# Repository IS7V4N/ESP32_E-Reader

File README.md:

# ESP32 E-Reader

A custom-built e-ink reading device based on the ESP32-C3, designed for everyday use. Built around a 4.2" e-ink display with a frontlight for reading in the dark environment, running a modified version of the [Crosspoint](https://github.com/crosspoint-reader/crosspoint-reader) open-source firmware adapted for custom hardware. The goal was to build a capable, low-cost alternative to commercial e-readers with full control over both hardware and software.

---
## Hardware License

The hardware designs in `/Hardware` are licensed under the
[CERN-OHL-W v2](Hardware/LICENSE).

## Hardware

> Building your own? See the [Build guide](Hardware/docs/Build%20guide.md) for step-by-step assembly instructions.

| Component  | Details                                             |
| ---------- | --------------------------------------------------- |
| MCU        | ESP32-C3 (4MB flash)                                |
| Display    | Good Display 4.2" grayscale e-ink panel             |
| Storage    | SD card (books, cache, user settings)               |
| Frontlight | TI TPS61169 PWM-controlled LED driver, 15V boost    |
| Battery    | 700mAh LiPo                                         |
| USB        | USB-C (charging + native USB via differential pair) |
| PCB        | 4-layer, custom KiCad design (Rev. B)               |

### PCB stack-up

```
F.Cu     — signal
GND      — full ground plane
PWR      — power distribution
B.Cu     — signal
```

Ground pour with stitching vias on both outer layers. EMI-sensitive boost converter traces kept compact.

### Power rails

| Rail     | Source                     | Purpose               |
| -------- | -------------------------- | --------------------- |
| 3.4–4.2V | LiPo battery               | System input          |
| 3.3V     | LDO                        | ESP32-C3, logic       |
| 5V       | USB-C input                | Charging              |
| ±20V     | Boost converter            | E-ink panel driver    |
| 15V      | Boost converter (TPS61169) | Frontlight LED driver |

### Power management

Three operating states optimized for battery life:

| State      | Description                                     | Wake latency |
| ---------- | ----------------------------------------------- | ------------ |
| Active     | Full speed, display updating                    | —            |
| Sleep      | Reduced CPU clock, peripherals idle             | Fast         |
| Deep sleep | µA range consumption, triggered by power button | Slow         |

The device enters Sleep automatically after a display update completes. Deep sleep is only used when powered off via the power button.

### Controls

| Button                        | Function                                                         |
| ----------------------------- | ---------------------------------------------------------------- |
| Left / Right / Back / Confirm | Context-sensitive navigation (current function shown on display) |
| Power button                  | Short press: page turn / Long press: power on/off                |

---

## Firmware

Based on [Crosspoint Reader](https://github.com/crosspoint-reader/crosspoint-reader) with modifications for custom hardware and 4MB flash constraint.

### What's changed from upstream

- **HalFrontlight** — new HAL driver for PWM-controlled frontlight via TPS61169
- **HalPowerManager** — smaller tweaks
- **HalGPIO** — GPIO, button layout adapted to custom PCB
- **partitions_4mb.csv** — custom partition scheme to fit 4MB flash (replaces upstream 16MB default)
- **platformio.ini** — 4MB build configuration
- **Display refresh** — modified refresh handling for Good Display 4.2" panel compatibility
- **Dictionary** — English → Hungarian word lookup in the EPUB reader (see [Dictionary](#dictionary))

See [`docs/4mb-build/`](Software/crosspoint-reader/docs/4mb-build/) for detailed documentation on the 4MB build process and known issues.

## Dictionary

Long-press **Confirm** (0.5 s) in an EPUB to enter dictionary mode. The four front buttons become a cursor:

| Button (left to right) | Short press  | Long press                  |
| ---------------------- | ------------ | --------------------------- |
| Left                   | cursor left  | —                           |
| Back                   | cursor up    | leave dictionary mode       |
| Confirm                | cursor down  | translate the selected word |
| Right                  | cursor right | —                           |

The translation (a few Hungarian words) appears in a popup, any button closes it.

The dictionary is a file on the SD card, `/dict/en-hu.dic` (about 4 MB, 118 000 word forms incl. inflections). It is
built on a PC with [`scripts/build_dict.py`](Software/crosspoint-reader/scripts/build_dict.py) from Wiktionary
(via [kaikki.org](https://kaikki.org)) with [FreeDict eng-hun](https://freedict.org) as a fallback; the script
documents the steps and the file format. Wiktionary data is CC BY-SA 4.0, FreeDict eng-hun is GPL-2.0+.

---

## Repository structure

```
ESP32_E-Reader/
├── Hardware/
│   ├── 3D CAD/                 — enclosure 3D models
│   ├── Bill Of Materials/      — BOM spreadsheets
│   ├── PCB/                    — KiCad project (Rev. B)
│   ├── REV-A/                  — Rev. A schematic/layout reference
│   └── LICENSE                 — CERN-OHL-W v2
├── Datasheets of Components/    — component datasheets (PDF)
└── Software/
    └── crosspoint-reader/       — firmware (fork of Crosspoint Reader)
        ├── src/                 — application source (activities, UI)
        ├── lib/                 — internal libraries (Epub engine, GfxRenderer, HAL, I18n)
        ├── open-x4-sdk/         — Xteink X4 community SDK (submodule)
        ├── docs/                — build docs, file formats, 4mb-build notes
        ├── scripts/             — build/codegen/debugging scripts
        ├── test/                — unit tests
        ├── platformio.ini       — build configuration
        └── LICENSE              — MIT
```

---

## Build

### Requirements

- [PlatformIO](https://platformio.org/)
- ESP32-C3 board with 4MB flash

### Steps

```bash
git clone https://github.com/IS7V4N/ESP32_E-Reader.git
cd ESP32_E-Reader
git submodule update --init --recursive
~/.platformio/penv/bin/pio run -e 4mb -t upload
```

---

## License
`/Hardware` are licensed under the
[CERN-OHL-W v2](Hardware/LICENSE).

Firmware modifications follow the license of the upstream [Crosspoint Reader](https://github.com/crosspoint-reader/crosspoint-reader) project.

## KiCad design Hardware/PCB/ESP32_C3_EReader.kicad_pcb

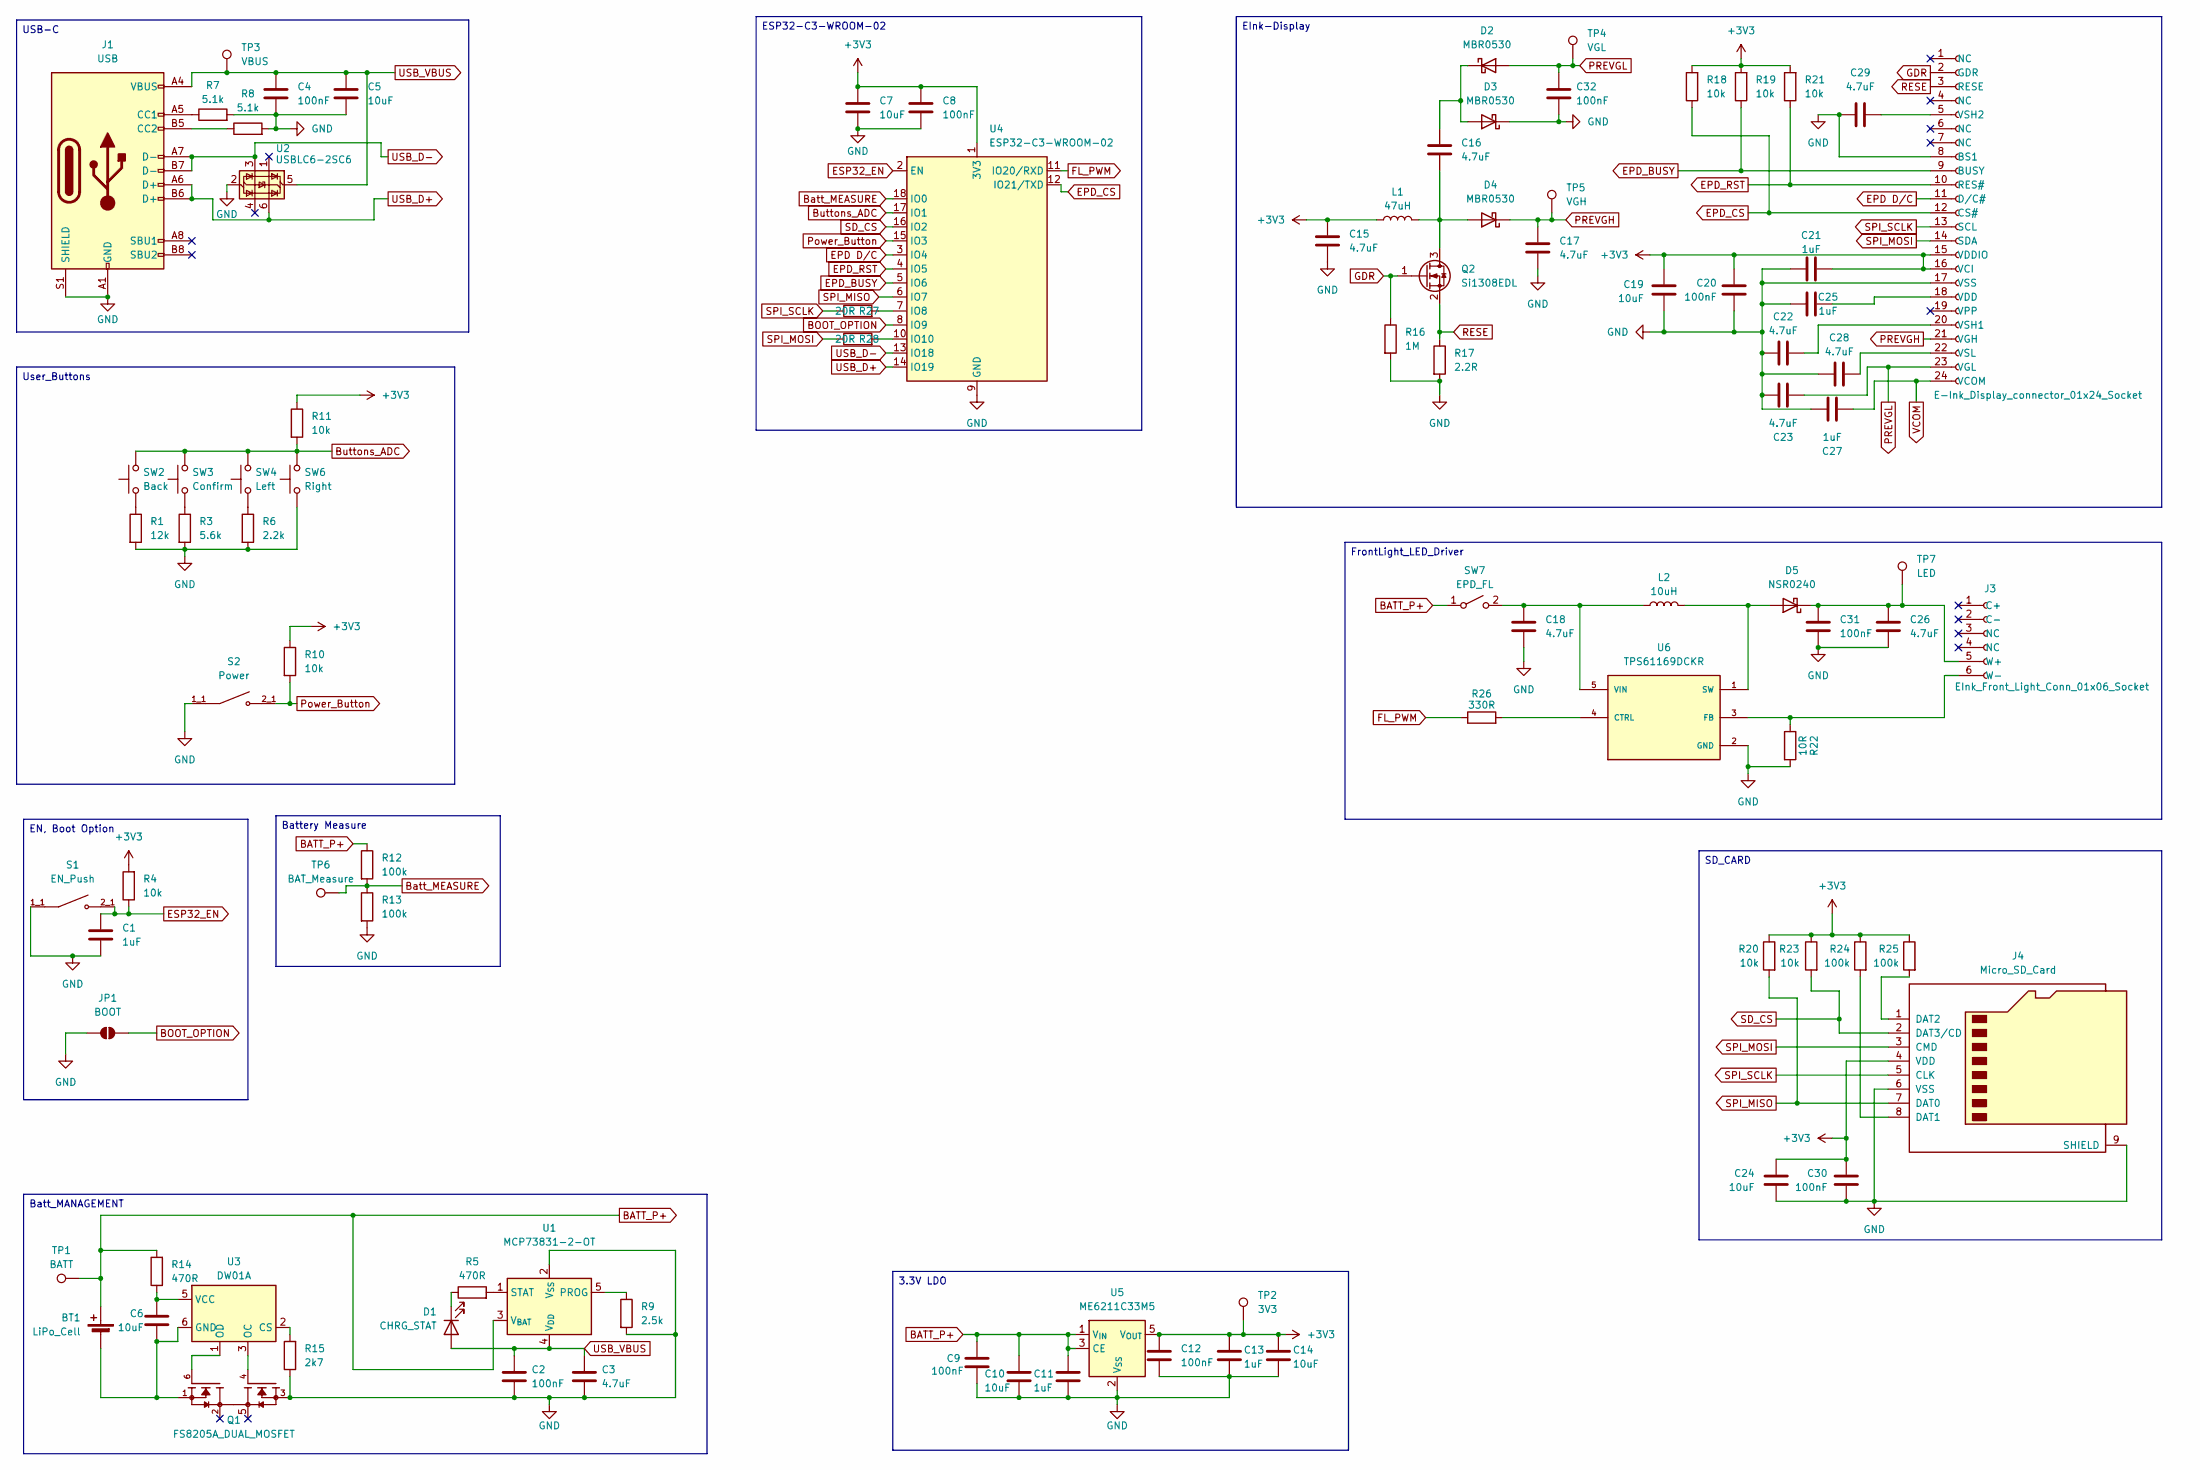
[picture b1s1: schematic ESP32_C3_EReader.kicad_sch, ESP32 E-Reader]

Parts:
BT1: LiPo_Cell; JST_PH_S2B-PH-K_1x02_P2.00mm_Horizontal
C1, C11, C13: 1uF; C_0603_1608Metric_Pad1.08x0.95mm_HandSolder
C2, C4, C8, C9, C12, C30: 100nF; C_0603_1608Metric_Pad1.08x0.95mm_HandSolder
C3, C15, C16, C17, C18, C22, C23, C26, C28, C29: 4.7uF; C_0805_2012Metric_Pad1.18x1.45mm_HandSolder
C5, C7, C10, C14, C24: 10uF; C_0603_1608Metric_Pad1.08x0.95mm_HandSolder
C6: 10uF; C_0603_1608Metric
C19: 10uF; C_0805_2012Metric_Pad1.18x1.45mm_HandSolder
C20: 100nF; R_0805_2012Metric_Pad1.20x1.40mm_HandSolder
C21, C25, C27: 1uF; C_0805_2012Metric_Pad1.18x1.45mm_HandSolder
C31, C32: 100nF; C_0805_2012Metric_Pad1.18x1.45mm_HandSolder
D1: CHRG_STAT; LED_0805_2012Metric_Pad1.15x1.40mm_HandSolder
D2, D3, D4: MBR0530; D_SOD-123
D5: NSR0240; D_SOD-323_HandSoldering
J1: USB; USB_C_Receptacle_GCT_USB4105-xx-A_16P_TopMnt_Horizontal
J2: E-Ink_Display_connector_01x24_Socket; Mirrored_Hirose_FH12-24S-0.5SH_1x24-1MP_P0.50mm_Horizontal
J3: EInk_Front_Light_Conn_01x06_Socket; XUNPU FPC-05FB-6PH20_1x06-1MP_P0.50mm_Horizontal
J4: Micro_SD_Card; microSD_HC_Hirose_DM3AT-SF-PEJM5
JP1: BOOT; SolderJumper-2_P1.3mm_Open_RoundedPad1.0x1.5mm
L1: 47uH; L_Panasonic_PCC-M0540M
L2: 10uH; L_Changjiang_FXL0420
Q1: FS8205A_DUAL_MOSFET; SOT-23-6_Handsoldering; PARTREV 1.7
Q2: Si1308EDL; SOT-323_SC-70
R1: 12k; R_0603_1608Metric_Pad0.98x0.95mm_HandSolder
R3: 5.6k; R_0603_1608Metric_Pad0.98x0.95mm_HandSolder
R4, R10, R11, R18, R19, R20, R21, R23: 10k; R_0603_1608Metric_Pad0.98x0.95mm_HandSolder
R5, R14: 470R; R_0603_1608Metric_Pad0.98x0.95mm_HandSolder
R6: 2.2k; R_0603_1608Metric_Pad0.98x0.95mm_HandSolder
R7, R8: 5.1k; R_0603_1608Metric_Pad0.98x0.95mm_HandSolder
R9: 2.5k; R_0603_1608Metric_Pad0.98x0.95mm_HandSolder
R12, R13, R24, R25: 100k; R_0603_1608Metric_Pad0.98x0.95mm_HandSolder
R15: 2k7; R_0603_1608Metric_Pad0.98x0.95mm_HandSolder
R16: 1M; R_0603_1608Metric_Pad0.98x0.95mm_HandSolder
R17: 2.2R; R_0805_2012Metric_Pad1.20x1.40mm_HandSolder
R22: 10R; R_0603_1608Metric_Pad0.98x0.95mm_HandSolder
R26: 330R; R_0603_1608Metric_Pad0.98x0.95mm_HandSolder
R27, R28: 20R; R_0603_1608Metric_Pad0.98x0.95mm_HandSolder
S1: EN_Push; SW_EVQ-P7C01P; PARTREV 2022.4
S2: Power; SW_EVQ-P7C01P; PARTREV 2022.4
SW2: Back; SW_SKRPACE010
SW3: Confirm; SW_SKRPACE010
SW4: Left; SW_SKRPACE010
SW6: Right; SW_SKRPACE010
SW7: EPD_FL; SW_SPDT_CK_JS102011SAQN
TP1: BATT; TestPoint_Pad_D1.5mm
TP2: 3V3; TestPoint_Pad_D1.5mm
TP3: VBUS; TestPoint_Pad_D1.5mm
TP4: VGL; TestPoint_Pad_D1.5mm
TP5: VGH; TestPoint_Pad_D1.5mm
TP6: BAT_Measure; TestPoint_Pad_D1.5mm
TP7: LED; TestPoint_Pad_D1.5mm
U1: MCP73831-2-OT; SOT-23-5
U2: USBLC6-2SC6; SOT-23-6
U3: DW01A; SOT-23-6
U4: ESP32-C3-WROOM-02
U5: ME6211C33M5; SOT-23-5
U6: TPS61169DCKR; SOT-353_SC-70-5; PARTREV A

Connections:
+3V3: C7.1, C8.1, C12.1, C13.1, C14.1, C15.1, C19.1, C20.1, C21.2, C24.1, C30.1, J2.15 (VDDIO), J2.16 (VCI), J4.4 (VDD), L1.1, R4.2, R10.1, R11.1, R18.2, R19.2, R20.1, R21.2, R23.1, R24.1, R25.1, TP2.1, U4.1 (3V3), U5.5 (V_{OUT})
BATT_P+: BT1.1 (+), C9.1, C10.1, C11.1, R12.1, R14.2, SW7.1 (A), TP1.1, U1.3 (V_{BAT}), U5.1 (V_{IN}), U5.3 (CE); also elsewhere on the board
BOOT_OPTION: JP1.2 (B), U4.8 (IO9)
Batt_MEASURE: R12.2, R13.1, TP6.1, U4.18 (IO0)
Buttons_ADC: R11.2, SW2.4, SW3.4 (2), SW4.4 (2), SW6.4 (2), U4.17 (IO1)
EPD D/C: J2.11 (D/C#), U4.3 (IO4)
EPD_BUSY: J2.9 (BUSY), R19.1, U4.5 (IO6)
EPD_CS: J2.12 (CS#), R18.1, U4.12 (IO21/TXD)
EPD_RST: J2.10 (RES#), R21.1, U4.4 (IO5)
ESP32_EN: C1.1, R4.1, S1.2_1, S1.2_2, U4.2 (EN)
FL_PWM: R26.1, U4.11 (IO20/RXD)
GDR: J2.2 (GDR), Q2.1 (G), R16.1
unnamed: D1.1 (K), R5.1
unnamed: C16.1, D2.1 (K), D3.2 (A)
unnamed: C16.2, D4.2 (A), L1.2, Q2.3 (D)
unnamed: D5.2 (A), L2.2, U6.1 (SW)
unnamed: C26.1, C31.1, D5.1 (K), J3.5 (W+), TP7.1
unnamed: J1.A5 (CC1), R7.1
unnamed: J1.B5 (CC2), R8.1
unnamed: C25.2, J2.18 (VDD)
unnamed: C22.2, J2.20 (VSH1)
unnamed: C29.2, J2.5 (VSH2)
unnamed: C28.2, J2.22 (VSL)
unnamed: J3.6 (W-), R22.1, U6.3 (FB)
unnamed: J4.8 (DAT1), R24.2
unnamed: J4.1 (DAT2), R25.2
unnamed: Q1.6 (G1), U3.1 (OD)
unnamed: Q1.4 (G2), U3.3 (OC)
unnamed: R1.1, SW2.1
unnamed: R3.1, SW3.1
unnamed: R6.1, SW4.1
unnamed 31: C18.1, L2.1, SW7.2 (B), U6.5 (VIN); also elsewhere on the board
unnamed: R9.1, U1.5 (PROG)
unnamed: R5.2, U1.1 (STAT)
unnamed: R15.2, U3.2 (CS)
unnamed: C6.1, R14.1, U3.5 (VCC)
unnamed: R27.2, U4.7 (IO8)
unnamed: R28.2, U4.10 (IO10)
unnamed: R26.2, U6.4 (CTRL)
PREVGH: C17.1, D4.1 (K), J2.21 (VGH), TP5.1
PREVGL: C23.2, C32.1, D2.2 (A), J2.23 (VGL), TP4.1
Power_Button: R10.2, S2.2_1, S2.2_2, U4.15 (IO3)
RESE: J2.3 (RESE), Q2.2 (S), R17.1
SD_CS: J4.2 (DAT3/CD), R23.2, U4.16 (IO2)
SPI_MISO: J4.7 (DAT0), R20.2, U4.6 (IO7)
SPI_MOSI: J2.14 (SDA), J4.3 (CMD), R28.1
SPI_SCLK: J2.13 (SCL), J4.5 (CLK), R27.1
USB_D+: J1.A6 (D+), J1.B6 (D+), U2.6 (I/O1), U4.14 (IO19)
USB_D-: J1.A7 (D-), J1.B7 (D-), U2.3 (I/O2), U4.13 (IO18)
USB_VBUS: C2.1, C3.1, C4.1, C5.1, D1.2 (A), J1.A4 (VBUS), J1.A9 (VBUS), J1.B4 (VBUS), J1.B9 (VBUS), TP3.1, U1.4 (V_{DD}), U2.5 (VBUS)
VCOM: C27.2, J2.24 (VCOM)

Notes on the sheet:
EN, Boot Option
3.3V LDO
EInk-Display
USB-C
SD_CARD
Batt_MANAGEMENT
User_Buttons
FrontLight_LED_Driver
Battery Measure
ESP32-C3-WROOM-02

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
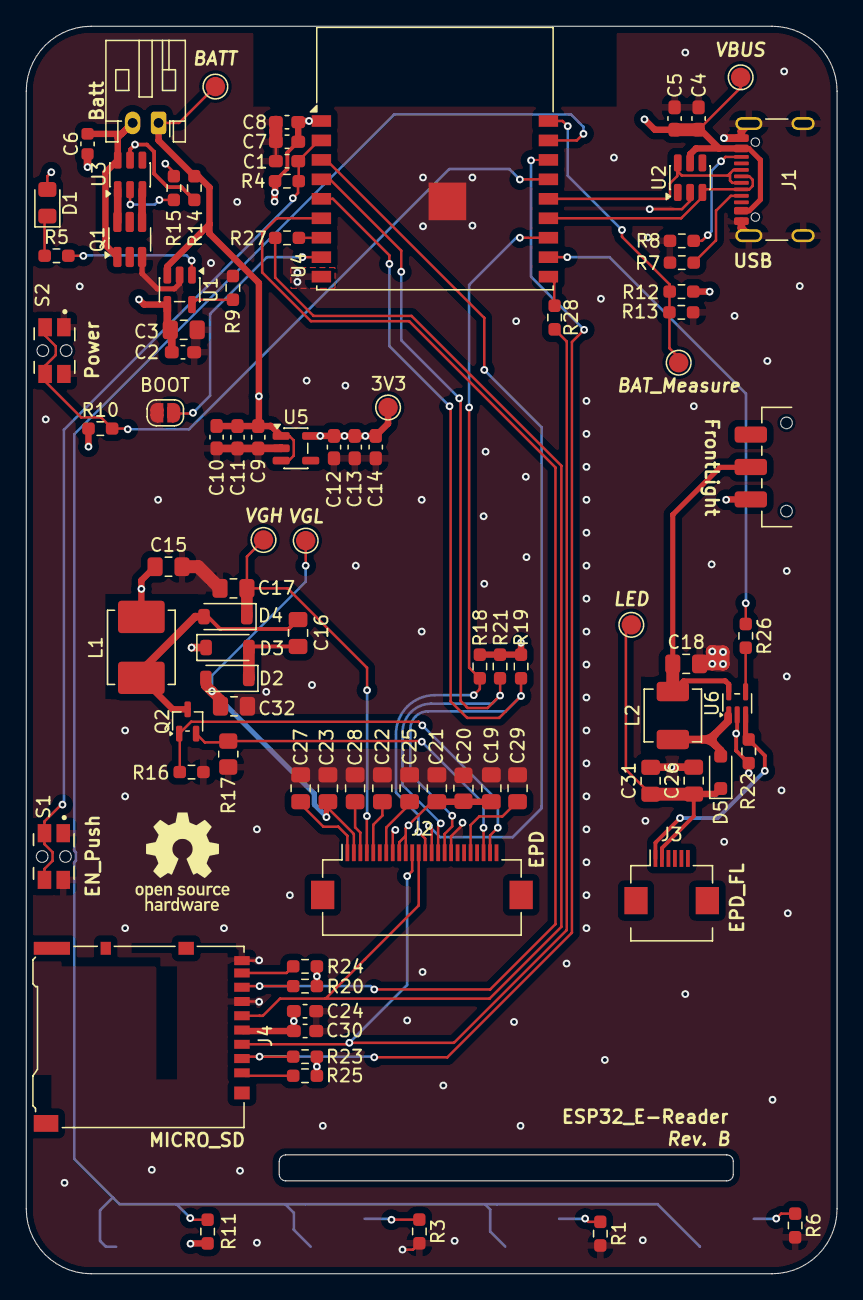
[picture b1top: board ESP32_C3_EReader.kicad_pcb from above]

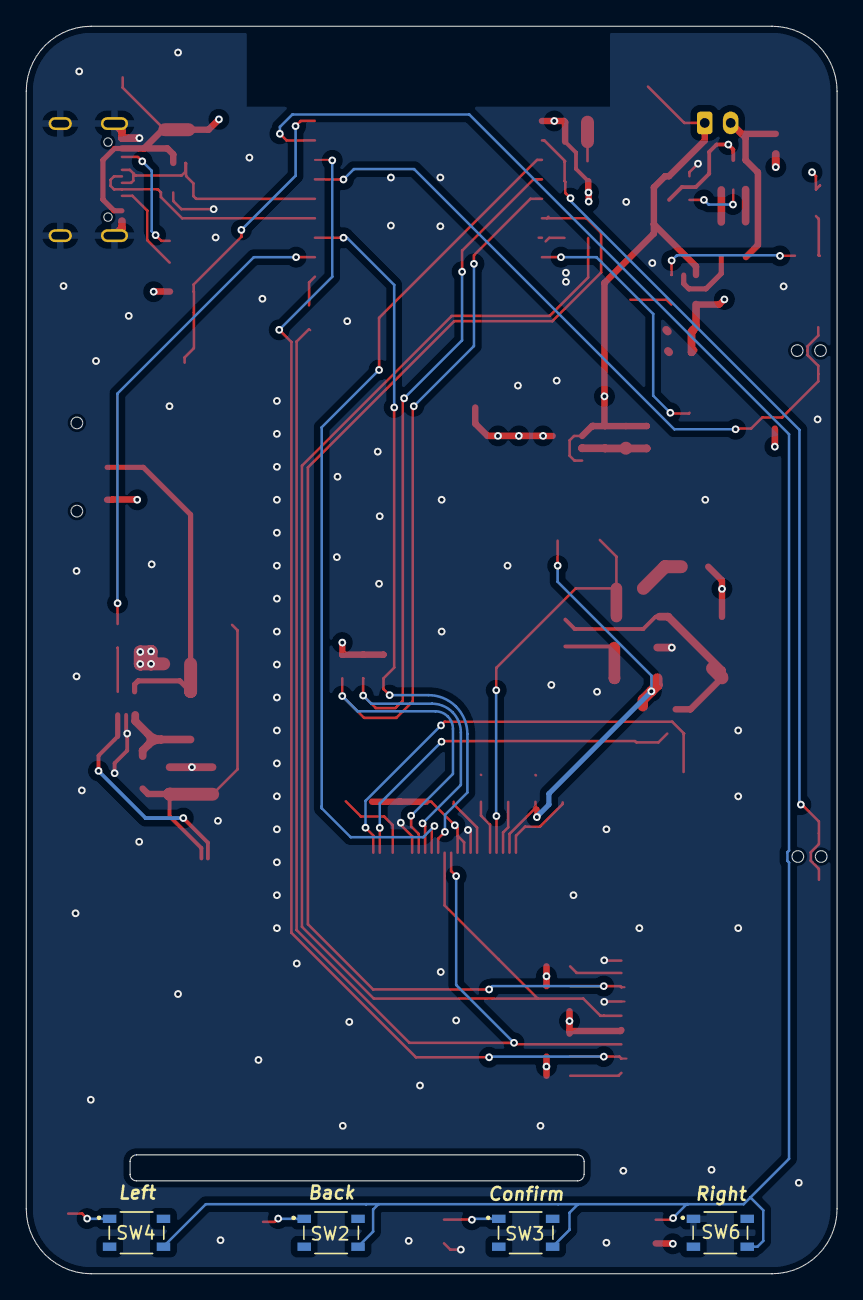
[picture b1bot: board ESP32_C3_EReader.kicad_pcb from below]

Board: 4 copper layers, 62.5 x 96.2 mm, 94 parts (4 on the bottom side), 53 nets.

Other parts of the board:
FrontLight: EPD_FL; SW_SPDT_CK_JS102011SAQN

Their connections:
BATT_P+: FrontLight.1 (A); also elsewhere on the board
unnamed 31: FrontLight.2 (B); also elsewhere on the board

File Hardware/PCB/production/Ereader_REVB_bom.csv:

Designator,Footprint,Quantity,Value,LCSC Part #
BT1,JST_PH_S2B-PH-K_1x02_P2.00mm_Horizontal,1,Batt,
"C1, C11, C13",0603,3,1uF,
"C10, C14, C24, C5, C6, C7",0603,6,10uF,
"C12, C2, C30, C4, C8, C9",0603,6,100nF,
"C15, C16, C17, C18, C22, C23, C26, C28, C29, C3",0805,10,4.7uF,
C19,0805,1,10uF,
"C20, C31, C32",0805,3,100nF,
"C21, C25, C27",0805,3,1uF,
D1,0805,1,CHRG_STAT,
"D2, D3, D4",D_SOD-123,3,MBR0530,
D5,D_SOD-323_HandSoldering,1,NSR0240,
FRONTLIGHT,SW_SPDT_CK_JS102011SAQN,1,EPD_FL,
J1,USB_C_Receptacle_GCT_USB4105-xx-A_16P_TopMnt_Horizontal,1,USB,
J2,Mirrored_Hirose_FH12-24S-0.5SH_1x24-1MP_P0.50mm_Horizontal,1,E-Ink_Display_connector_01x24_Socket,
J3,XUNPU FPC-05FB-6PH20_1x06-1MP_P0.50mm_Horizontal,1,EInk_Front_Light_Conn_01x06_Socket,
J4,microSD_HC_Hirose_DM3AT-SF-PEJM5,1,Micro_SD_Card,
L1,L_Panasonic_PCC-M0540M,1,47uH,
L2,L_Changjiang_FXL0420,1,10uH,
Q1,SOT-23-6_Handsoldering,1,FS8205A_DUAL_MOSFET,
Q2,SOT-323_SC-70,1,Si1308EDL,
R1,0603,1,12k,
"R10, R11, R18, R19, R20, R21, R23, R4",0603,8,10k,
"R12, R13, R24, R25",0603,4,100k,
"R14, R5",0603,2,470R,
R15,0603,1,2.7k,
R16,0603,1,1M,
R17,0805,1,2.2R,
R22,0603,1,10R,
R26,0603,1,330R,
"R27, R28",0603,2,20R,
R3,0603,1,5.6k,
R6,0603,1,2.2k,
"R7, R8",0603,2,5.1k,
R9,0603,1,2.5k,
S1,SW_EVQ-P7C01P,1,EN_Push,
S2,SW_EVQ-P7C01P,1,Power,
SW2,SW_SKRPACE010,1,Back,
SW3,SW_SKRPACE010,1,Confirm,
SW4,SW_SKRPACE010,1,Left,
SW6,SW_SKRPACE010,1,Right,
TP1,TestPoint_Pad_D1.5mm,1,BATT,
TP2,TestPoint_Pad_D1.5mm,1,3V3,
TP3,TestPoint_Pad_D1.5mm,1,VBUS,
TP4,TestPoint_Pad_D1.5mm,1,VGL,
TP5,TestPoint_Pad_D1.5mm,1,VGH,
TP6,TestPoint_Pad_D1.5mm,1,BAT_Measure,
TP7,TestPoint_Pad_D1.5mm,1,LED,
U1,SOT-23-5,1,MCP73831-2-OT,
U2,SOT-23-6,1,USBLC6-2SC6,
U3,SOT-23-6,1,DW01A,
U4,ESP32-C3-WROOM-02,1,ESP32-C3-WROOM-02,
U5,SOT-23-5,1,ME6211C33M5,
U6,SOT-353_SC-70-5,1,TPS61169DCKR,
